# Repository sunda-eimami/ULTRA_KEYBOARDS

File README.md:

# first — 44キー分割無線キーボード (Ergogen → KiCad)

片側 22 キー（メイン 3行×6列 ＋ 親指 4キー）、Kailh Choc v2 ホットスワップ、
**Seeed XIAO nRF52840 Plus** の分割無線キーボード。`config.yaml` から Ergogen で
左右 2 枚の KiCad PCB を自動生成し、Freerouting による自動配線・DRC・ガーバー生成まで済んでいます。

| 全 44 キー配置 | 配線済み PCB (左/右) |
| --- | --- |
|  |  |

## 状態 (2026-09-02)

- `kicad/first_left.kicad_pcb` / `kicad/first_right.kicad_pcb` — **配線済み・DRC 違反 0・未配線 0**
- `gerbers/first_left.zip` / `gerbers/first_right.zip` — **発注用ガーバー**（JLCPCB 等にそのままアップロード可）

## 使い方

```sh
npm install          # ergogen をローカルにインストール
npm run build        # = ergogen . --clean   → output/ に未配線 PCB を再生成
npm run build:svg    # 外形 SVG も出力
```

> **注意**: `output/` はビルドのたびに完全に上書きされます。配線済みデータは `kicad/`、
> 発注データは `gerbers/` にあり、これらはビルドでは消えません。config を変更したら
> 「`npm run build` → `output/pcbs/*.kicad_pcb` を `kicad/` にコピー → 再ルーティング」が必要です。

## ディレクトリ構成

```
.
├── config.yaml              Ergogen 設定 = 回路の一次ソース (キー配置・外形・ネット定義)
├── footprints/
│   ├── ceoloide/            ceoloide/ergogen-footprints (Choc, ダイオード, JST, 電源SW 等) ※CC BY-NC-SA 4.0
│   └── local/mcu_xiao_nrf52840_plus.js   XIAO nRF52840 Plus (Seeed 公式 KiCad データの座標から作成)
├── output/                  Ergogen 生成物 (未配線。ビルドごとに上書き)
├── kicad/                   配線済み PCB (Freerouting + 手修正、DRC クリーン)
├── gerbers/                 発注用ガーバー zip
└── docs/                    プレビュー画像
```

## 設計メモ

- **配列**: 列は外側から `outer, pinky, ring, middle, index, inner`、行は下から `bottom, home, top`。
  Columnar stagger は pinky 基準で ring +6.3 / middle +8.8 / index +4.3 / inner +2.3 mm。
  親指 4 キーは `rotate: -90`、半径 140mm の円弧上に 8° ピッチで扇状配置。
- **左右別基板**: XIAO は USB・リセットボタンが上面にあるためリバーシブル化できず、
  左手用 (`first_left`) と右手用 (`first_right`) を別々に生成・配線しています。
- **実装面**: スイッチソケット・ダイオード = 裏面 / XIAO・JST・電源スイッチ = 表面。
  XIAO は castellated パッドで表面に直付け。バッテリー (502030) は MCU 下の「ベイ」裏面。
- **ピン割当 (ZMK: `&xiao_d n`)**
  | 用途 | ピン |
  |---|---|
  | 列 outer→inner | D0 D1 D2 D3 D4 D5 |
  | 親指 t1→t4 | D2 D3 D4 D5 (列を流用) |
  | 行 top / home / bottom / thumb | D9 / D8 / D7 / D6 |
  | 電源 | JST(BAT_P) → 電源SW → VBAT (モジュール裏パッド、基板のスルーホール経由で半田付け) |
  | リセット | XIAO 本体ボタン (1回=リセット、素早く2回=ブートローダ) |
  | 空き | D10 (+ Plus 裏面の D11〜D19) |
- **ダイオード**: 1N4148W (SOD-123)、col2row。帯マーク (カソード) が行ネット側。
- **マウントホール**: M2 NPTH ×4/枚。

## 発注 (JLCPCB の例)

1. [jlcpcb.com](https://jlcpcb.com) で `gerbers/first_left.zip` をアップロード → 2層 / 1.6mm / 1oz / HASL でそのまま注文 (最低5枚)
2. `first_right.zip` も同様に注文 (別設計扱い)
3. 部品: Choc v2 スイッチ×44、Choc ソケット×44、1N4148W×44+予備、XIAO nRF52840 Plus×2、
   JST PH 2P×2、電源SW (Alps SSSS811101)×2、502030 LiPo×2

## メンテナンスの流れ

回路図ファイル (.kicad_sch) は存在しません。**`config.yaml` が回路図に相当する一次ソース**で、
接続定義 (from/to) はすべてそこに書かれています。回路を変更するときは config を編集して再生成し、
Freerouting で再ルーティングします (このリポジトリの履歴と配線図ドキュメントを参照)。

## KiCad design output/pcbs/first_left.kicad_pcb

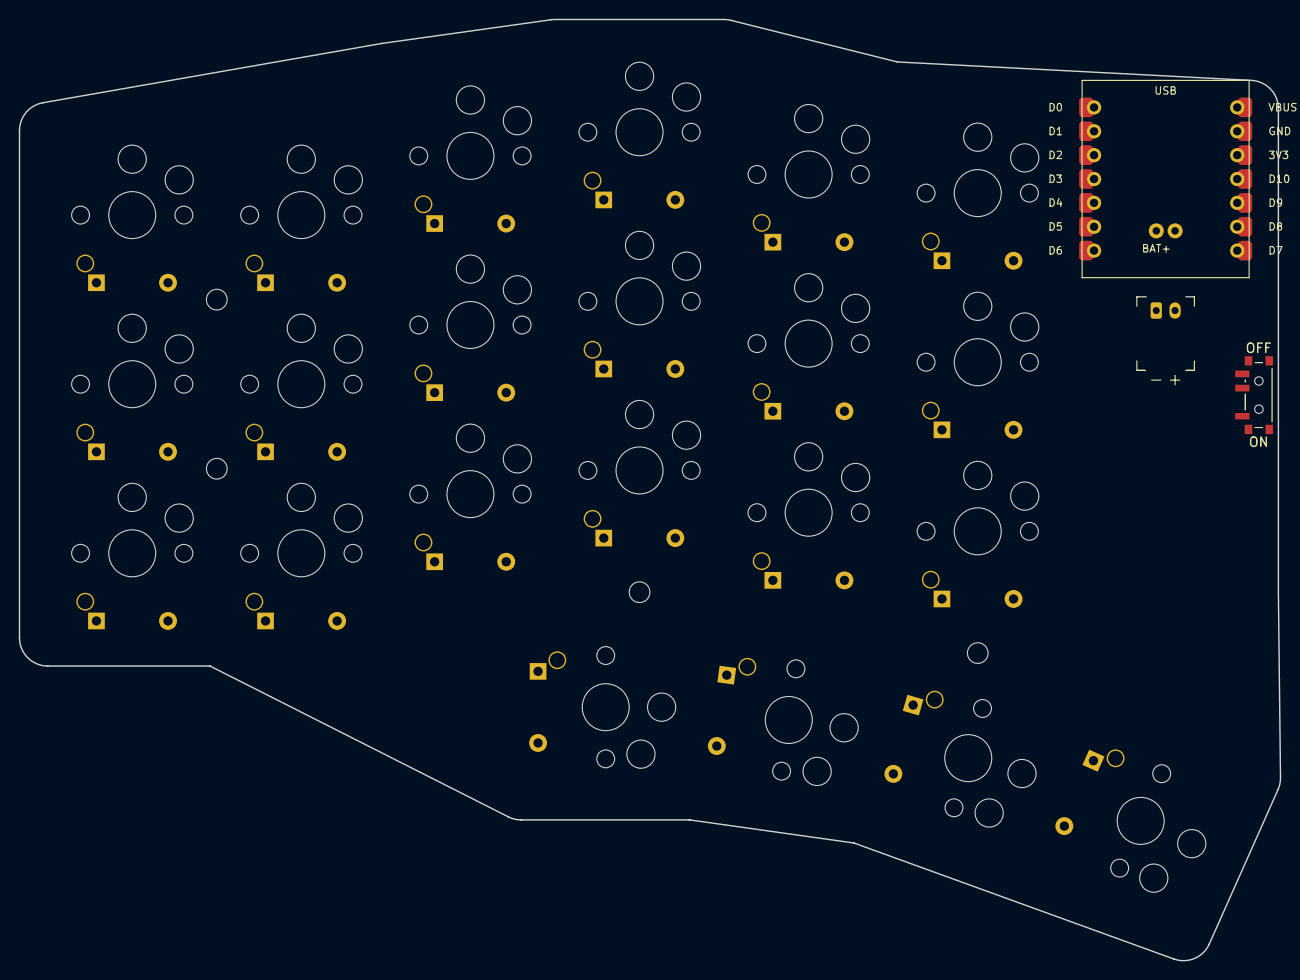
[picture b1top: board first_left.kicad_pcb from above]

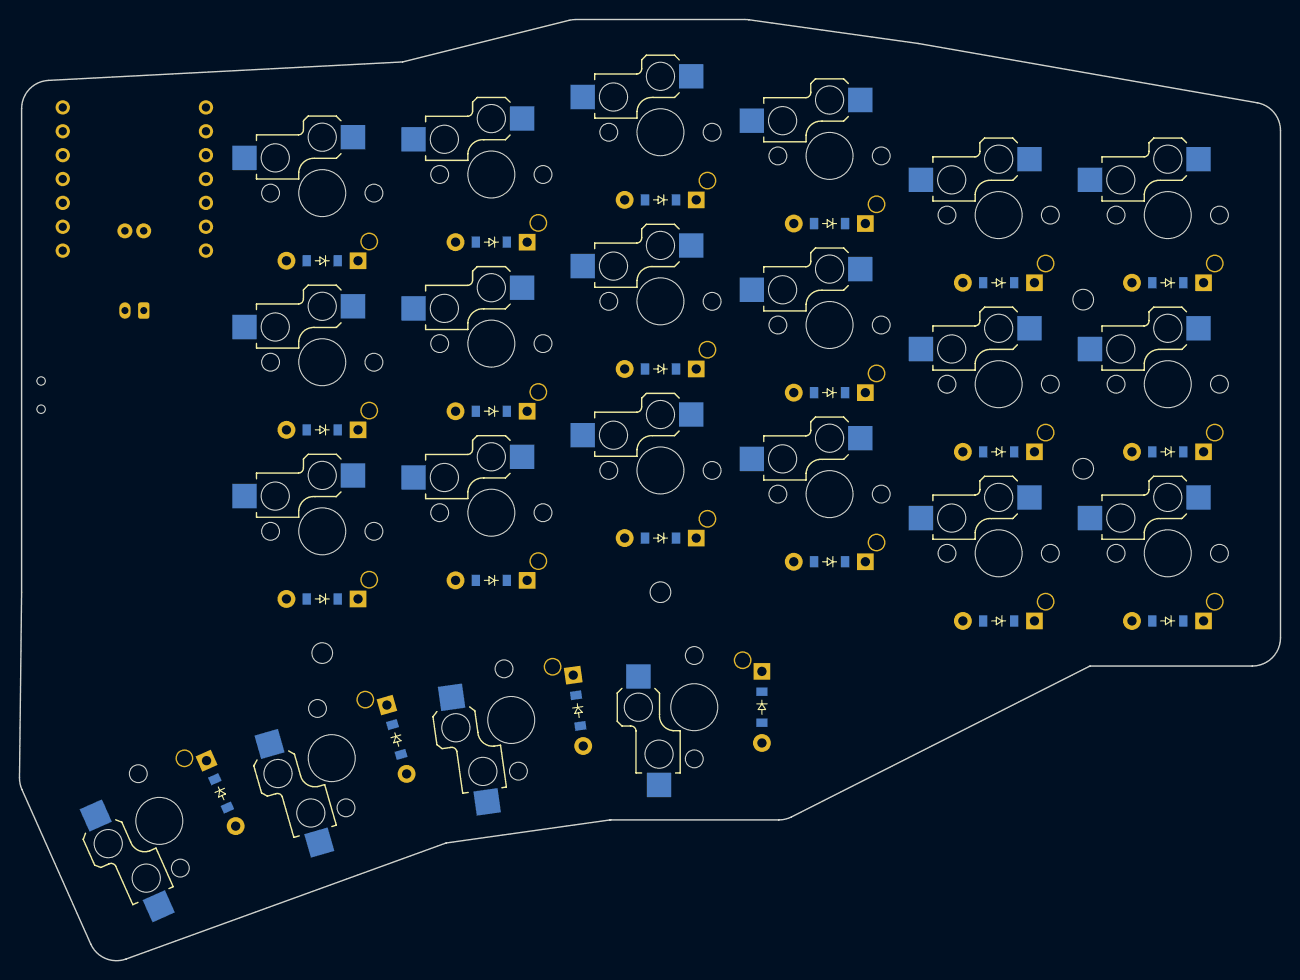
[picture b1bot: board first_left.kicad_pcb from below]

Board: 2 copper layers, 134.2 x 100.2 mm, 51 parts (44 on the bottom side), 35 nets, no tracks yet.

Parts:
D1, D2, D3, D4, D5, D6, D7, D8, D9, D10, D11, D12, D13, D14, D15, D16, D17, D18, D19, D20, D21, D22: diode_tht_sod123
JST1: battery_connector_jst_ph_2
MCU1: mcu_xiao_nrf52840_plus
MH1, MH2, MH3, MH4: mounting_hole_npth
PWR1: power_switch_smd_side
S1, S2, S3, S4, S5, S6, S7, S8, S9, S10, S11, S12, S13, S14, S15, S16, S17, S18, S19, S20, S21, S22: switch_choc_v1_v2

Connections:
BAT_P: JST1.2, PWR1.1
D0: MCU1.1, S1.1, S2.1, S3.1
D1: MCU1.2, S4.1, S5.1, S6.1
D2: MCU1.3, S7.1, S8.1, S9.1, S19.1
D3: MCU1.4, S10.1, S11.1, S12.1, S20.1
D4: MCU1.5, S13.1, S14.1, S15.1, S21.1
D5: MCU1.6, S16.1, S17.1, S18.1, S22.1
D6: D19.1, D20.1, D21.1, D22.1, MCU1.7
D7: D1.1, D4.1, D7.1, D10.1, D13.1, D16.1, MCU1.14
D8: D2.1, D5.1, D8.1, D11.1, D14.1, D17.1, MCU1.13
D9: D3.1, D6.1, D9.1, D12.1, D15.1, D18.1, MCU1.12
GND: JST1.1, MCU1.9, MCU1.29
VBAT: MCU1.28, PWR1.2
index_bottom: D13.2, S13.2
index_home: D14.2, S14.2
index_top: D15.2, S15.2
inner_bottom: D16.2, S16.2
inner_home: D17.2, S17.2
inner_top: D18.2, S18.2
middle_bottom: D10.2, S10.2
middle_home: D11.2, S11.2
middle_top: D12.2, S12.2
outer_bottom: D1.2, S1.2
outer_home: D2.2, S2.2
outer_top: D3.2, S3.2
pinky_bottom: D4.2, S4.2
pinky_home: D5.2, S5.2
pinky_top: D6.2, S6.2
ring_bottom: D7.2, S7.2
ring_home: D8.2, S8.2
ring_top: D9.2, S9.2
t1_thumb: D19.2, S19.2
t2_thumb: D20.2, S20.2
t3_thumb: D21.2, S21.2
t4_thumb: D22.2, S22.2
